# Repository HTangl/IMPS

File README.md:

# IMPS
Variable Impedance Selector  

The IMPS is a simple pcb made to allow switching between different sets of resistors to emulate output impedance. It was made to facilitate easy testing of impedance effects on headphones and iems.  

Parts list is as follows  

10 - 1/4 watt metal film resistors of varying values  
You can use any values you want but the original inteded values were R1-10, R2-20, R3-50, R4-75, R5-100  

2 - surface mount 3.5mm ports  
There are most likely a lot of different generic ports that will work here, I used some uxcell ones  
https://a.co/d/fRi1UGk  

1 - 2P6T rotary switch  
This needs to have surface mount pins not through hole legs as the holes on the PCB were not designed to fit those  
https://a.co/d/1c0tU72  

1 - 3.5mm male to 3.5mm male cable  
For connecting the IMPS input to desired source device

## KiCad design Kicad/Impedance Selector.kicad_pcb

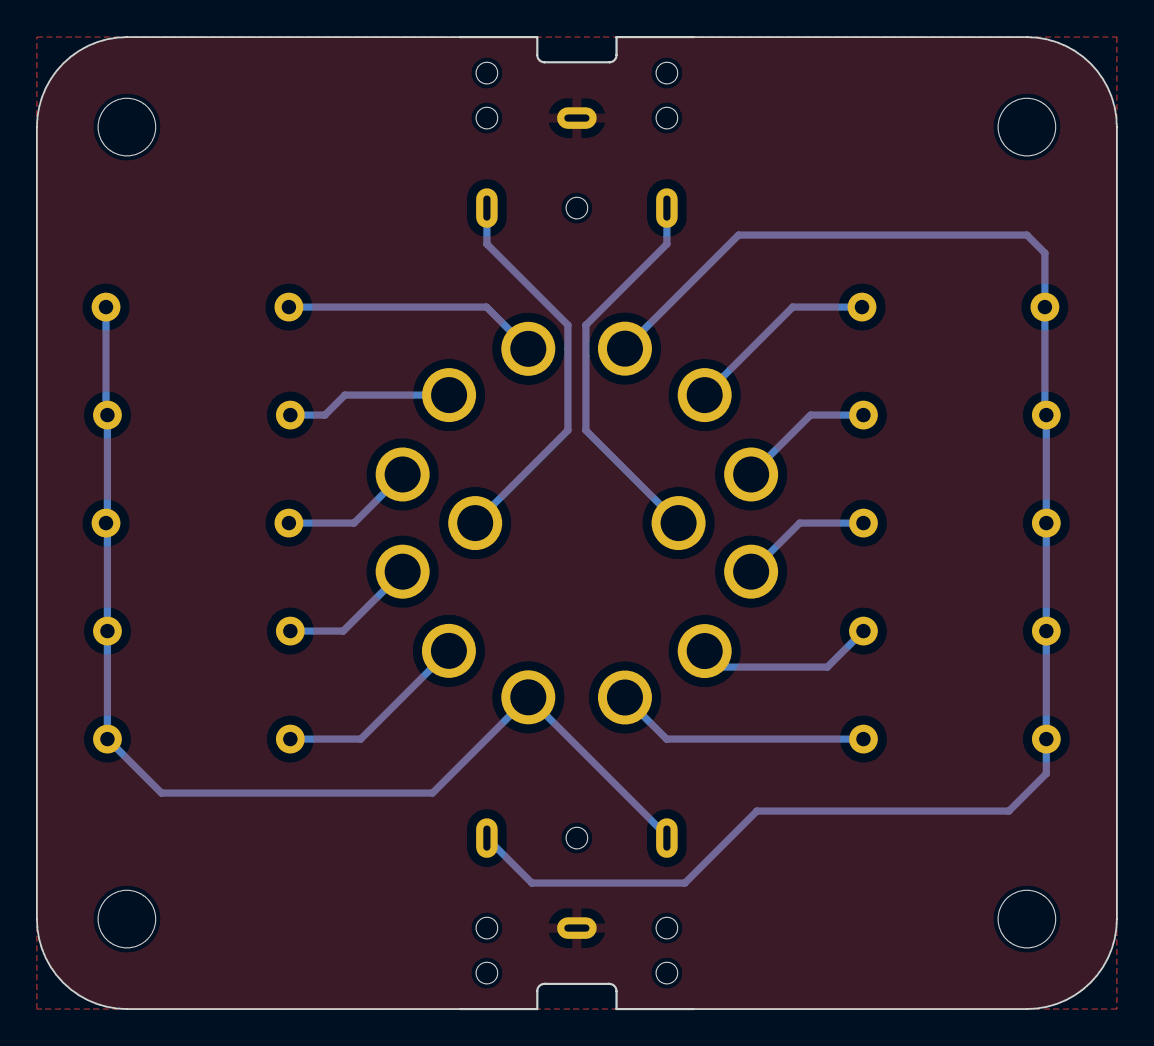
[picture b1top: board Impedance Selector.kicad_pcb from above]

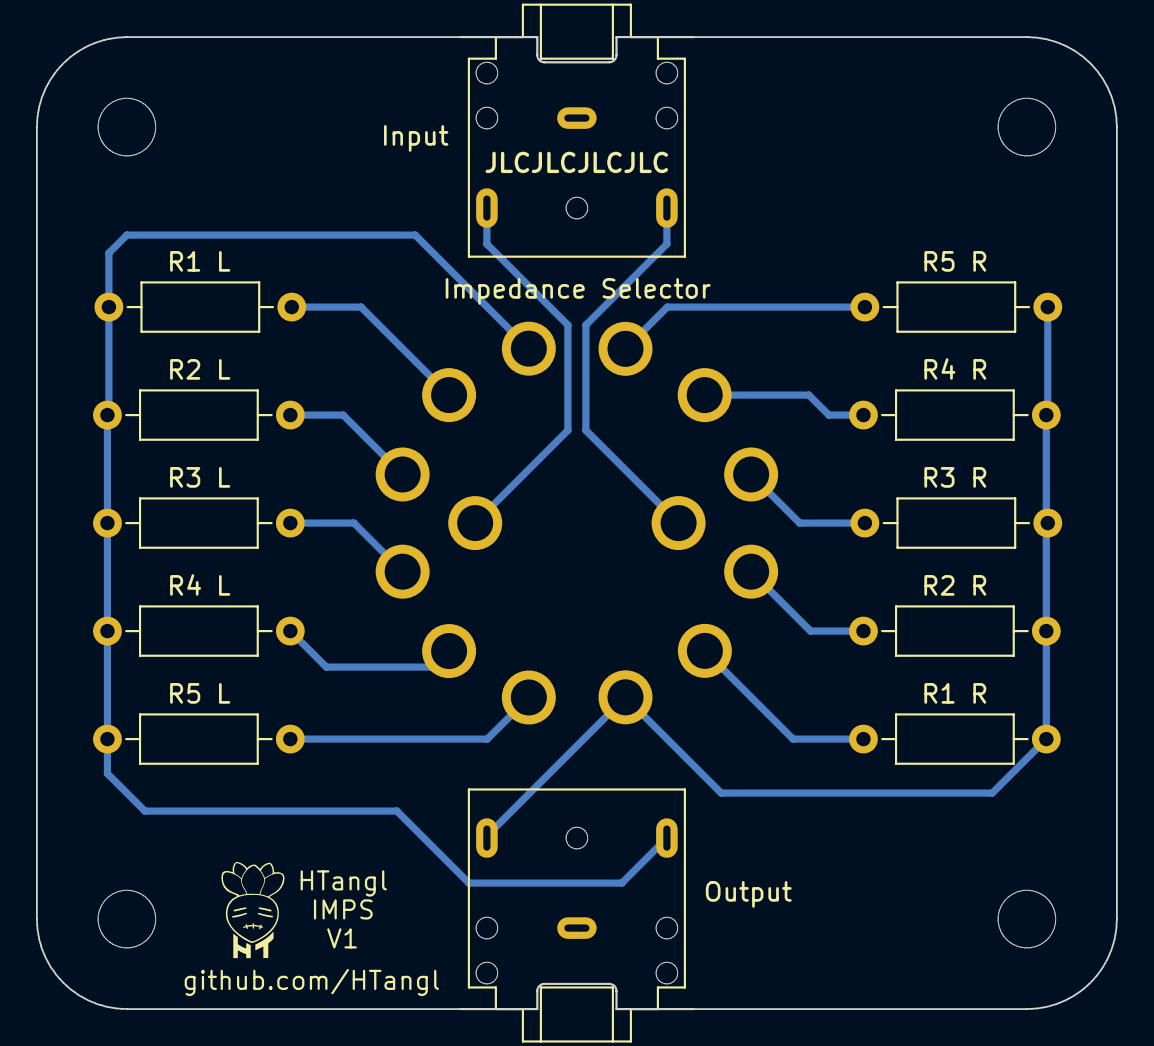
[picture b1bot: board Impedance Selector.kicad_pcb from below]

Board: 2 copper layers, 60.0 x 54.0 mm, 13 parts (12 on the bottom side), 15 nets.

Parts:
J1: Input; Jack_3.5mm_CUI_SJ1-3523N_Horizontal
J2: Output; Jack_3.5mm_CUI_SJ1-3523N_Horizontal
R1 L, R1 R: 10; R_Axial_DIN0207_L6.3mm_D2.5mm_P10.16mm_Horizontal
R2 L, R2 R: 20; R_Axial_DIN0207_L6.3mm_D2.5mm_P10.16mm_Horizontal
R3 L, R3 R: 50; R_Axial_DIN0207_L6.3mm_D2.5mm_P10.16mm_Horizontal
R4 L, R4 R: 75; R_Axial_DIN0207_L6.3mm_D2.5mm_P10.16mm_Horizontal
R5 L, R5 R: 100; R_Axial_DIN0207_L6.3mm_D2.5mm_P10.16mm_Horizontal
SW1: Impedance Selector; Rotary_Switch_2P6T

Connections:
GND: J1.S, J2.S
unnamed: J1.R, SW1.14
unnamed: J1.T, SW1.13
unnamed: J2.R, R1 R.2, R2 R.2, R3 R.2, R4 R.2, R5 R.2, SW1.7
unnamed: J2.T, R1 L.2, R2 L.2, R3 L.2, R4 L.2, R5 L.2, SW1.1
unnamed: R1 L.1, SW1.2
unnamed: R1 R.1, SW1.8
unnamed: R2 L.1, SW1.3
unnamed: R2 R.1, SW1.9
unnamed: R3 L.1, SW1.4
unnamed: R3 R.1, SW1.10
unnamed: R4 L.1, SW1.5
unnamed: R4 R.1, SW1.11
unnamed: R5 L.1, SW1.6
unnamed: R5 R.1, SW1.12

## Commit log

2024-06-01 Create LICENSE
